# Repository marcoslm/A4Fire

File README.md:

# A4Fire - Circuito de Auto-disparo

Este proyecto fue desarrollado en 2015 para cumplir con los requerimientos específicos de **Enrique García** para su proyecto personal. El código es sencillo y el circuito es fácil de construir para cualquier aficionado a la electrónica.

## Descripción del Proyecto

El firmware implementa un circuito de auto-disparo para joysticks y gamepads compatibles con las normas **Atari/Commodore**, y es compatible con otros sistemas como **MSX** o **Amstrad CPC**. Está diseñado para funcionar con un microcontrolador **PIC 10F200** y fue creado usando el entorno de desarrollo **MPLAB X v2.05** con el compilador **XC8**.

A4Fire fue desarrollado como parte del proyecto del joystick A4 de Enrique García. Puedes encontrar más información sobre su proyecto en su [canal de YouTube](https://www.youtube.com/channel/UCb7_NkehBK6dyK2aAPUDlYA).

## Estructura del Proyecto

El proyecto está organizado en dos secciones principales:

1. **Circuito**: Contiene los archivos necesarios para el diseño del circuito y la placa PCB.
   - Archivos de diseño en Eagle.
   - Esquema y detalles de las conexiones.
   - Archivos PDF con las vistas previas del diseño (`Bottom.pdf` es la cara de las pistas y `TopSilk.pdf` es la serigrafía). Los archivos están listos para imprimir a escala real y fabricar el circuito de manera casera.

2. **Firmware**: Incluye el código fuente y el archivo compilado (.hex) listo para ser grabado en el microcontrolador PIC.
   - `main.c`: Código fuente del firmware.
   - `A4-autofire-PIC10F200.hex`: Archivo compilado para grabar en el PIC 10F200.

## Instrucciones

1. Utiliza los archivos PDF para fabricar la placa de circuito de forma casera. El archivo `Bottom.pdf` contiene la vista de las pistas, y el archivo `TopSilk.pdf` es la serigrafía para imprimir a escala real.
   
2. El archivo `A4-autofire-PIC10F200.hex` se puede flashear en un microcontrolador **PIC 10F200** usando cualquier programador compatible o universal, como los populares programadores de la serie **TL866**.

## Esquema de Conexiones

| SERIGRAFÍA | NOMBRE      | DESCRIPCIÓN                                                        |
|------------|-------------|--------------------------------------------------------------------|
| FO         | FIRE OUT    | Salida de disparo hacia el ordenador                               |
| G          | GROUND      | Tierra                                                             |
| +5         | +5 VOLTS    | Alimentación a 5V (desde el conector o batería)                    |
| FI         | FIRE IN     | Botón de disparo (botón físico del joystick)                       |
| SW1        | SWITCH      | Interruptor para activar/desactivar autofire                       |
| SPEED      | SPEED SEL   | Selección de velocidad (1-2 = Normal, 2-3 = Turbo) 

## Licencia

Este proyecto está licenciado bajo la licencia MIT. Eres libre de usar, modificar y distribuir el proyecto tanto para fines personales como comerciales. Además, puedes sublicenciar y/o vender copias del proyecto. Consulta el archivo [LICENSE](./LICENSE) para más detalles.

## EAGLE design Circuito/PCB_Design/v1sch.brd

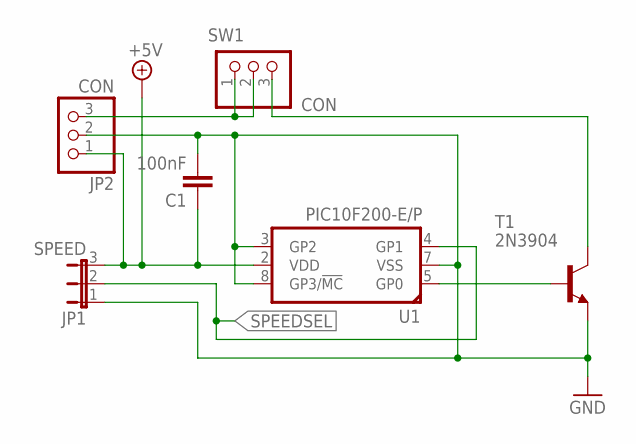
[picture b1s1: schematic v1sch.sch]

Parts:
C1: 100nF; C025-025X050
JP1: SPEED; JP2
JP2: CON; 1X03
SW1: CON; 1X03
T1: 2N3904; TO92; MPN 2N3904
U1: PIC10F200-E/P; DIL08

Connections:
+5V: C1.1, JP1.3, JP2.1, U1.2 (VDD)
GND: C1.2, JP1.1, JP2.2, T1.3 (E), U1.3 (GP2), U1.7 (VSS), U1.8 (GP3/!MC!)
unnamed: SW1.3, T1.1 (C)
unnamed: JP2.3, SW1.1, SW1.2
unnamed: T1.2 (B), U1.5 (GP0)
SPEEDSEL: JP1.2, U1.4 (GP1)

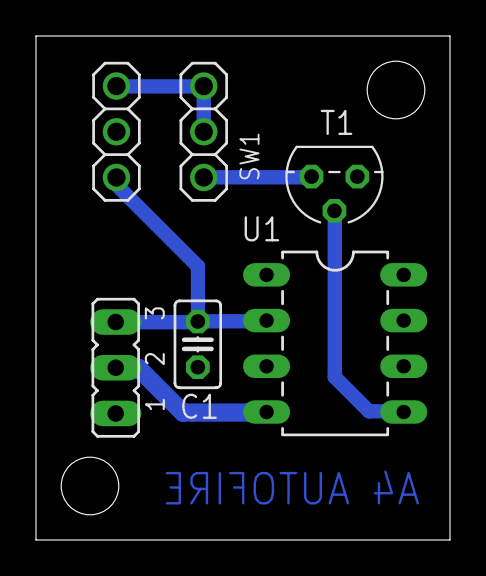
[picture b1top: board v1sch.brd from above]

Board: 2 copper layers, 23.0 x 28.0 mm, 6 parts (0 on the bottom side), 6 nets.

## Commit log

2024-09-07 Commit Inicial
